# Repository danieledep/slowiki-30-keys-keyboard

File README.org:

* 30-keys-keyboard

  Handheld tactile switch keyboard for Teensy 3.2 compatible boards.      
  It consists of a modified fork of:
  - [[https://github.com/AnthonyDiGirolamo/teensy-thumb-keyboard][AnthonyDiGirolamo/teensy-thumb-keyboard]]

*** v1.0 Photo
    [[./hardware/v1.0/images/wikiboard.jpg]]

** Features
   - 30 keys arranged in a 3x10 matrix (uses 13 pins on the microcontroller).
   - Silkscreen has a qwerty layout, the first row keys act as a number if pressed longer.
   - Lead free ENIG-RoHs surface finish with 2oz copper.
   - SPI, I2C, and 2 additional GPIOs broken out.
   - Each pin along the edge of the Teensy is connected to one extra pin in the
     prototyping area.
   - Beginner friendly through hole soldering.
   - Layout is completely customizable in the firmware.

** Parts list for a fully working keyboard

   - 1x [[https://www.pjrc.com/store/teensy32.html][Teensy 3.2]] or [[https://www.pjrc.com/store/teensylc.html][Teensy LC]]. A [[https://www.tindie.com/products/TleraCorp/butterfly-stm32l433-development-board/][Butterfly STM32L433]] will also work (though not
     as a USB keyboard).
   - 10x 1N4148 Zener Diodes
   - 30x Panasonic EVQ-PAC04M Tacticle Switches. These are the quieter and higher
     quality switches. Some are available at [[https://www.digikey.com/products/en?keywords=EVQ-PAC04M][digikey]]. If you wish to use the 3d
     printed faceplate the overall switch height must be 4.3mm. These models will
     also work: EVQ-PAD04M EVQ-PAE04M EVQ-PAG04M. Otherwise any standard 6x6mm
     momentary switch will work.

** Firmware

   - The layout for USB keyboarding is defined in the ~usb_key_matrix~ variable
     in [[https://github.com/danieledep/slow-wiki/blob/main/30-keys-wikiboard/firmware/LayoutThumbKeyboard.h#L109][LayoutThumbKeyboard.h]]

   - If you don't need a USB keyboard and are rolling your own hardware project
     then you can focus on the layout defined by the ~ascii_key_matrix~ variable
     in [[https://github.com/danieledep/slow-wiki/blob/main/30-keys-wikiboard/firmware/LayoutThumbKeyboard.h#L74][LayoutThumbKeyboard.h]]

   - USB can be disabled by commenting out define ~USE_TEENSY_USB_KEYBOARD~.

   - All the keyboardy goodness is handled by the ~keyboard_update();~ function
     called from inside the standard Arduino ~loop()~.

   - If you don't need the keys to behave like a keyboard you can gut most of
     that example and just use ~key_matrix.update();~ The KeyboardMatrix class
     handles reading the button states.

*** Compiling on Windows machines

    1. Using a Teensy 3.2 or Teensy LC follow these directions for downloading
       and installing the teensyduino add-on to the Arduino environment:
       https://www.pjrc.com/teensy/td_download.html

    2. Once you have both installed. Launch the Arduino IDE and check what
       version of teensyduino is installed by going to *Help > About
       Arduino*. The about window for me shows *Arduino 1.8.9* in the upper left
       and *Teensyduino 1.46* in the upper right.

    3. Download the code archive from the firmware folder

    4. Extract that folder and move the firmware folder to:
       ~C:\Users\Username\Documents\Arduino\firmware~

    5. Rename the ~firmware~ folder to ~teensy32_thumb_keyboard~

       The full path should be:
       ~C:\Users\Username\Documents\Arduino\teensy32_thumb_keyboard~

       And these files should exist inside there:

       #+BEGIN_SRC text
         KeyboardMatrix.cpp
         KeyboardMatrix.h
         LayoutCommon.h
         LayoutThumbKeyboard.h
         LinkedList.h
         slowiki-30-keys-keyboard.ino
       #+END_SRC

    6. Open
       ~C:\Users\User\Documents\Arduino\teensy32_thumb_keyboard\teensy32_thumb_keyboard.ino~
       in the arduino IDE.

    7. In the *Tools* menu select *USB Type > Serial + Keyboard + Mouse + Joystick*

    8. Click the verify or upload buttons in the toolbar. If compilation is
       successful you should see a message like:

       #+BEGIN_SRC text
         Sketch uses 27920 bytes (10%) of program storage space. Maximum is 262144 bytes.
         Global variables use 6680 bytes (10%) of dynamic memory, leaving 58856 bytes for local variables. Maximum is 65536 bytes.
       #+END_SRC

** Alternate Versions

   - [[https://github.com/AnthonyDiGirolamo/i2c-thumb-keyboard][i2c-thumb-keyboard]]
   - [[https://github.com/AnthonyDiGirolamo/teensy-thumb-keyboard][teensy-thumb-keyboard]]

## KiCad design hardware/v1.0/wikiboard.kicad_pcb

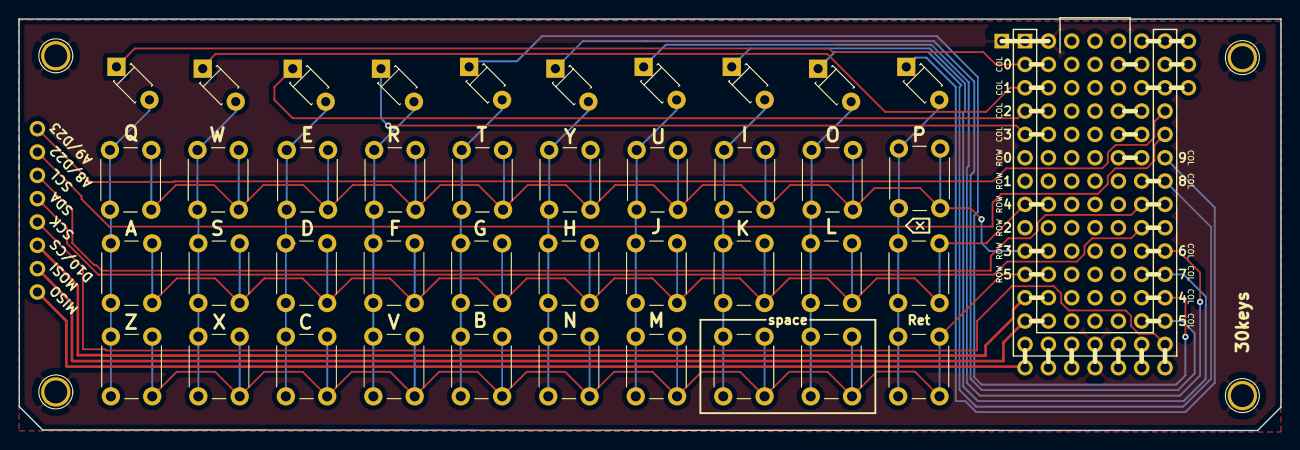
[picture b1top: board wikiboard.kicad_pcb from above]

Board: 2 copper layers, 137.4 x 44.8 mm, 47 parts (0 on the bottom side), 32 nets.

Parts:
D1, D2, D3, D4, D5, D6, D7, D8, D9, D10: D_Zener_Small; D_T-1_P5.08mm_Horizontal
J1, J2, J3, J4: Conn_01x01; 2.5MountingHole
J5: Conn_01x08_Male; PinSocket_1x08_P2.54mm_Vertical
J7: Conn_01x01_Male; PinHeader_1x01_P2.54mm_Vertical
SW31, SW32, SW33, SW34, SW35, SW36, SW37, SW38, SW39, SW40, SW41, SW42, SW43, SW44, SW45, SW46, SW47, SW48, SW49, SW50, SW51, SW52, SW53, SW54, SW55, SW56, SW57, SW58, SW59, SW60: SW_Push; SW_PUSH_6mm
U1: Teensy3.2; Teensy32_InnerProto

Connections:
22-A8: J5.2, U1.29
23-A9: J5.1, U1.30
COL0: D1.1, U1.2
COL1: D2.1, U1.3
COL2: D3.1, U1.4
COL3: D4.1, U1.5
COL4: D5.1, U1.22
COL5: D6.1, U1.21
COL6: D7.1, U1.24
COL7: D8.1, U1.23
COL8: D9.1, U1.27
COL9: D10.1, U1.28
CS: J5.6, U1.12
DIN: J5.8, U1.14
DOUT: J5.7, U1.13
GND: J1.1, J2.1, J3.1, J4.1, J7.1, U1.1, U1.17
unnamed: D1.2, SW31.1, SW41.1, SW51.1
unnamed: D2.2, SW32.1, SW42.1, SW52.1
unnamed: D3.2, SW33.1, SW43.1, SW53.1
unnamed: D4.2, SW34.1, SW44.1, SW54.1
unnamed: D5.2, SW35.1, SW45.1, SW55.1
unnamed: D6.2, SW36.1, SW46.1, SW56.1
unnamed: D7.2, SW37.1, SW47.1, SW57.1
unnamed: D8.2, SW38.1, SW48.1, SW58.1
unnamed: D9.2, SW39.1, SW49.1, SW59.1
unnamed: D10.2, SW40.1, SW50.1, SW60.1
ROW3: SW31.2, SW32.2, SW33.2, SW34.2, SW35.2, SW36.2, SW37.2, SW38.2, SW39.2, SW40.2, U1.10
ROW4: SW41.2, SW42.2, SW43.2, SW44.2, SW45.2, SW46.2, SW47.2, SW48.2, SW49.2, SW50.2, U1.8
ROW5: SW51.2, SW52.2, SW53.2, SW54.2, SW55.2, SW56.2, SW57.2, SW58.2, SW59.2, SW60.2, U1.11
SCK: J5.5, U1.20
SCL: J5.3, U1.26
SDA: J5.4, U1.25

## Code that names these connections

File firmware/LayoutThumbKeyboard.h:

#ifndef LAYOUTTHUMBKEYBOARD_H
#define LAYOUTTHUMBKEYBOARD_H

#include <Arduino.h>
#include "LayoutCommon.h"

#define NUM_ROWS 3
#define NUM_COLS 10

// USB Facing Up
// Row Pins
#define ROW0 4
#define ROW1 5
#define ROW2 7
#define ROW3 8
#define ROW4 6
#define ROW5 9
// Column Pins
#define COL0 0
#define COL1 1
#define COL2 2
#define COL3 3
#define COL4 15
#define COL5 14
#define COL6 17
#define COL7 16
#define COL8 20
#define COL9 21

// // USB Facing Down
// // Row Pins
// #define ROW0 18
// #define ROW1 19
// #define ROW2 21
// #define ROW3 22
// #define ROW4 20
// #define ROW5 23
// // Column Pins
// #define COL0 14
// #define COL1 15
// #define COL2 16
// #define COL3 17
// #define COL4 1
// #define COL5 0
// #define COL6 3
// #define COL7 2
// #define COL8 6
// #define COL9 7

const uint8_t row_pins[] =
  {
   ROW3,
   ROW4,
   ROW5,
  };

const uint8_t col_pins[] =
  {
   COL0,
   COL1,
   COL2,
   COL3,
   COL4,
   COL5,
   COL6,
   COL7,
   COL8,
   COL9,
  };

const char ascii_key_matrix[3][NUM_ROWS][NUM_COLS] =
  {
   // Base Layer
   {
    {'q',         'w',        'e',         'r',         't', 'y', 'u',      'i', 'o',         'p'},
    {'a',         's',        'd',         'f',         'g', 'h', 'j',      'k', 'l',         '\b'},
    {'z',         'x',        'c',         'v',         'b', 'n', 'm',      ' ', ' ',         '\n'},
   },
   // Shift Layer
   {
    {'Q', 'W', 'E', 'R', 'T', 'Y', 'U', 'I', 'O',  'P'},
    {'A', 'S', 'D', 'F', 'G', 'H', 'J', 'K', 'L',  '\b'},
    {'Z', 'X', 'C', 'V', 'B', 'N', 'M', ' ', ' ',  '\n'},
   },
   // Fn Layer
   {
    {0,                    0,              0,                0,                      0, 0,                    0,                0,                0,  0},
    {0,                    0,              0,                0,                      0, 0,                    0,                0,                0,  0},
    {0,                    0,              0,                0,                      0, 0,                    0,                0,                0,  0},
   },
  };


// for all keycodes see:
// ~/apps/arduino-1.8.5/hardware/teensy/avr/cores/teensy3/keylayouts.h
// https://www.pjrc.com/teensy/td_keyboard.html
const uint16_t usb_key_matrix[NUM_ROWS][NUM_COLS] =
  // Base Layer
  {
   {KEY_Q,             KEY_W,            KEY_E,           KEY_R,           KEY_T,     KEY_Y,     KEY_U,     KEY_I,     KEY_O,             KEY_P},
   {KEY_A,             KEY_S,            KEY_D,           KEY_F,           KEY_G,     KEY_H,     KEY_J,     KEY_K,     KEY_L,             KEY_BACKSPACE},
   {KEY_Z,             KEY_X,            KEY_C,           KEY_V,           KEY_B,     KEY_N,     KEY_M,     KEY_SPACE, KEY_SPACE,         KEY_ENTER},
  };

#endif

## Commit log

2021-07-15 Rename 30-keys-wikiboard.ino to slowiki-30-keys-keyboard.ino
